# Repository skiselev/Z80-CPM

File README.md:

# Z80-CPM
RCBus Z80 CPU, 512 KiB SRAM, and 512 KiB Flash ROM module for RCBus systems designed using discrete logic

## Table of Content
* [Overview](#overview)
  * [Specifications](#specifications)
* [Assembly Instructions](#assembly-instructions)
* [Hardware Documentation](#hardware-documentation)
  * [Schematic and PCB Layout](#schematic-and-pcb-layout)
  * [Input/Output Ports](#inputoutput-ports)
  * [Connectors](#connectors)
  * [Bill of Materials](#bill-of-materials)
* [Release Notes](#release-notes)
  * [Changes](#changes)
  * [Known Issues](#known-issues)
* [Red Tape](#red-tape)
  * [Licensing](#licensing)
  * [Trademarks](#trademarks)

## Overview
Z80-CPM is an RCBus and RC2014* compatible module, designed to run [RomWBW](https://github.com/wwarthen/RomWBW) firmware including CP/M, ZSDOS, and various applications under these OSes. Z80-CPM combines functionality of the following RC2014* modules on a single module, thus saving space on the backplane:
* Z80 CPU Module
* 512k ROM 512k RAM Module - Simplified version, compatible with RomWBW firmware
* Clock and Reset Module

Minimal CP/M computer system can be built using Z80-CPM module, a backplane, and a serial port module, for example Steve Cousins' [SC716](https://smallcomputercentral.com/sc716-rcbus-z80-sio-2-serial-module/) or [SC725](https://smallcomputercentral.com/sc725-rcbus-serial-and-timer-module/) Z80 SIO modules, or MC68B50 ACIA. A Compact Flash module can be added for additional storage. For a compact system, a 3-slot [SC723](https://smallcomputercentral.com/sc723-rcbus-backplane-3/) can be used.

### Specifications
* Processor: Zilog* Z80 CPU (CMOS version - Z84C00)
* Memory: 512 KiB SRAM, 512 KiB Flash ROM, RomWBW compatible memory pager
* Bus: RCBus, RC2014* compatible
* Microprocessor Supervisor for system reset generation

## Assembly Instructions

Please refer to [Assembly Instructions](Assembly_Instructions.md) document

## Hardware Documentation

### Schematic and PCB Layout

* [Schematic - Version 1.0](KiCad/Z80-CPM-Schematic-1.0.pdf)
* [PCB Layout - Version 1.1](KiCad/Z80-CPM-Board-1.1.pdf)
* [PCB Layout - Version 1.0](KiCad/Z80-CPM-Board-1.0.pdf)

### Memory Configuration Input/Output Ports
Z80-CPM supports up to 512 KiB of RAM and up to 512 KiB of Flash ROM. It has a simple memory bank switching mechanism with two 32 KiB memory banks, inspired by Steve Cousin's [SC602](https://smallcomputercentral.com/rcbus/sc600-series/sc602-rcbus-z80-memory-module/) Memory Module. This memory bank mechanism provides minimal required functionality for the RomWBW RCZ80_std.rom image to be used without any modifications.
The upper 32 KiB bank is always mapped to the top 32 KiB of the physical RAM. The lower 32 KiB bank can be mapped to any 32 KiB size page in the physical memory. The memory page is selected by writting either 0x78 or 0x79 I/O ports, that are mapped to the same page select register.

#### 0x78 or 0x79 - Memory Page Select Register (Write-only)

Port       | Bit # | Function                               | Value
-----------|-------|----------------------------------------|-----------------------
0x78, 0x79 | 0     | Not implemented                        | Can be set to either 0 or 1
0x78, 0x79 | 5-1   | Page number for bank #0 0x0000-0xr7FFF | 0-31 - Page number
0x78, 0x79 | 7-6   | Not implemented                        | Should be set to 0

* Notes:
  * The register is reset to '0' on power-on or reset, which maps the lower 32 KiB of the Flash ROM to bank #0.
  * Bit 5 selects between the Flash ROM (bit 5 = 0) and the RAM (bit 5 = 1).

### Jumpers Settings

#### JP1 - RAM Size Configuration

Jumper Position | Description
----------------|------------
1-2             | 512 KiB SRAM
2-3             | 128 KiB SRAM

#### JP2 - Connect on-board oscillator clock to the CPU

Jumper Position | Description
----------------|------------
**Closed**      | X1 oscillator is connected to the CPU
Open            | X1 oscillator is not connected to the CPU

#### JP3 - Connect the RCBus CLK1 signal to the CPU

Jumper Position | Description
----------------|------------
**Closed**      | CLK1 signal is connected to the CPU
Open            | CLK1 signal is not connected to the CPU

#### JP2 and JP3 Configuration Notes

The module supports the following options for the CPU clock:
1. **Default**: CPU uses the clock frequency generated by the X1 oscillator, and the X1 clock frequency is output to CLK1 signal on RCBus. Install both JP2 and JP3 for this option.
2. CPU uses the clock frequency provided by another module on RCBus. Install only JP3 for this option.
3. CPU uses the clock frequency generated by the X1 oscillator, while other modules use different CLK1 signal. This might be useful, for example, when running the CPU on a frequency other than 7.3728 MHz. Install only JP2 for this option.

### Connectors

#### J1 - RC2014* Bus
Pin | Signal Name | Description                             | Pin | Signal Name | Description
--- | ----------- | --------------------------------------- | --- | ----------- | -----------
1   | A15         | Address A15; Output                    | 41  | p41         | Reserved; Not connected
2   | A14         | Address A14; Output                     | 42  | /BAI        | Bus Acknowledge In; Not connected
3   | A13         | Address A13; Output                     | 43  | /BAO        | Bus Acknowledge Out; Not connected
4   | A12         | Address A12; Output                     | 44  | p44         | Reserved; Not connected
5   | A11         | Address A11; Output                     | 45  | p45         | Reserved; Not connected
6   | A10         | Address A10; Output                     | 46  | p46         | Reserved; Not connected
7   | A9          | Address A9; Output                      | 47  | p47         | Reserved; Not connected
8   | A8          | Address A8; Output                      | 48  | p48         | Reserved; Not connected
9   | A7          | Address A7; Output                      | 49  | A23         | Address A23; Not connected
10  | A6          | Address A6; Output                      | 50  | A22         | Address A22; Not connected
11  | A5          | Address A5; Output                      | 51  | A21         | Address A21; Not connected
12  | A4          | Address A4; Output                      | 52  | A20         | Address A20; Not connected
13  | A3          | Address A3; Output                      | 53  | A19         | Address A19; Output
14  | A2          | Address A2; Output                      | 54  | A18         | Address A18; Output
15  | A1          | Address A1; Output                      | 55  | A17         | Address A17; Output
16  | A0          | Address A0; Output                      | 56  | A16         | Address A16; Output
17  | GND         | Ground                                  | 57  | GND         | Ground
18  | VCC         | Power Supply - +5V                      | 58  | VCC         | Power Supply - +5V
19  | /M1         | Machine Cycle One; Output               | 59  | /RFSH       | DRAM refresh; Output
20  | /RESET      | Reset; Output                           | 60  | PAGE         | Page ROM/RAM input; Not connected
21  | CLK1        | CPU Clock; Output                       | 61  | CLK2        | UART Clock; Not connected
22  | /INT        | Interrupt; Input                        | 62  | /BUSACK     | DMA Bus Acknowledge; Output
23  | /MREQ       | Memory Request; Output                  | 63  | /HALT       | Halt; Output
24  | /WR         | Write Request; Output                   | 64  | /BUSREQ     | DMA Bus Request; Input
25  | /RD         | Read Request; Output                    | 65  | /WAIT       | Wait; Input
26  | /IORQ       | Input/Output Request; Output            | 66  | /NMI        | Non-maskable Interrupt; Input
27  | D0          | Data D0; Input/Output                   | 67  | D8          | Data D8; Input/Output; Not connected
28  | D1          | Data D1; Input/Output                   | 68  | D9          | Data D9; Input/Output; Not connected
29  | D2          | Data D2; Input/Output                   | 69  | D10         | Data D10; Input/Output; Not connected
30  | D3          | Data D3; Input/Output                   | 70  | D11         | Data D11; Input/Output; Not connected
31  | D4          | Data D4; Input/Output                   | 71  | D12         | Data D12; Input/Output; Not connected
32  | D5          | Data D5; Input/Output                   | 72  | D13         | Data D13; Input/Output; Not connected
33  | D6          | Data D6; Input/Output                   | 73  | D14         | Data D14; Input/Output; Not connected
34  | D7          | Data D7; Input/Output                   | 74  | D15         | Data D15; Input/Output; Not connected
35  | TX          | Channel 1, Transmit Data; Not Connected | 75  | TX2         | Channel 2, Transmit Data; Not Connected
36  | RX          | Channel 1, Receive Data; Not Connected  | 76  | RX2         | Channel 2, Receive Data; Not Connected
37  | /IRQ1       | Interrupt Request 1; Not connected      | 77  | /IRQ2       | Interrupt Request 2; Not connected
38  | IEI         | Interrupt Enable In; Not connected      | 78  | p78         | Reserved; Not connected
39  | IEO         | Interrupt Enable Out; Not connected     | 79  | p79         | Reserved; Not connected
40  | USER4       | User Pin 4; Not connected               | 80  | USER8       | User Pin 8; Not connected

### Bill of Materials

#### Version 1.0

Mouser projects - All components except of the PCB and the CPU:
* [Z80-CPM project](https://www.mouser.com/Tools/Project/Share?AccessID=cf00dde769)
  * Note that optional CPU supervisor parts: U9 DS1233 CPU supervisor, C11 1 nF capacitor, and SW1 tactile switch are included in this project.

Z80-CPM project on Tindie:
* [Complete kit](https://www.tindie.com/products/weird/z80-cpm-rcbus-module-kit/).
* [Z80-CPU PCB](https://www.tindie.com/products/weird/z80-cpm-rcbus-module-pcb/).

Component type     | Reference | Description                                 | Quantity | Possible sources and notes 
------------------ | --------- | ------------------------------------------- | -------- | --------------------------
PCB                |           | Z80-CPM PCB - Version 1.0                   | 1        | Buy from my Tindie store: [Complete kit](https://www.tindie.com/products/weird/z80-cpm-rcbus-module-kit/); [Z80-CPM PCB](https://www.tindie.com/products/weird/z80-cpm-rcbus-module-pcb/), or order from a PCB manufacturer of your choice using provided Gerber or KiCad files
Integrated Circuit | U1        | Z84C00xxVEG - Z80 CPU, CMOS, 44 pin PLCC    | 1        | Mouser [692-Z84C0010VEG](https://www.mouser.com/ProductDetail/692-Z84C0010VEG)
Integrated Circuit | U2        | SST39SF040 - 512 KiB Flash ROM, 32 pin PLCC | 1        | Mouser [804-39SF0407CNHE](https://www.mouser.com/ProductDetail/804-39SF0407CNHE)
Integrated Circuit | U3        | AS6C4008 - 512 KiB SRAM, 32 pin DIP         | 1        | Mouser [913-AS6C4008-55PCN](https://www.mouser.com/ProductDetail/913-AS6C4008-55PCN)
Integrated Circuit | U4        | 74AHCT174 - Hex D-Type Flip Flop, 16 pin DIP | 1       | Mouser [595-SN74AHCT174N](https://www.mouser.com/ProductDetail/595-SN74AHCT174N)
Integrated Circuit | U5        | 74HCT138 - 3-to-8 Decoder, 16 pin DIP       | 1        | Mouser [595-CD74HCT138E](https://www.mouser.com/ProductDetail/595-CD74HCT138E)
Integrated Circuit | U6, U7    | 74AHCT32 - Quad 2-Input OR Gate, 14 pin DIP | 2        | Mouser [595-SN74AHCT32N](https://www.mouser.com/ProductDetail/595-SN74AHCT32N)
Integrated Circuit | U8        | 74AHCT00 - Quad 2-Input NAND Gate, 14 pin DIP | 1      | Mouser [595-SN74AHCT00N](https://www.mouser.com/ProductDetail/595-SN74AHCT00N)
Integrated Circuit | U9        | DS1233-5 - CPU Supervisor, 5V, TO-92-3      | 1        | Mouser [700-DS1233-5](https://www.mouser.com/ProductDetail/700-DS1233-5). Note U9 is an optional on-board CPU supervisor.
Oscillator         | X1        | 7.3728 MHz, CMOS oscillator, half can       | 1        | Mouser [774-MXO45HS-3C-7.3](https://www.mouser.com/ProductDetail/774-MXO45HS-3C-7.3) or [520-2200B-073](https://www.mouser.com/ProductDetail/520-2200B-073)
Pin Header         | J1        | 40x2 pin header, 2.54 mm pitch, right angle | 1        | Mouser [737-PH2RA-80-UA](https://www.mouser.com/ProductDetail/737-PH2RA-80-UA), [517-5121TG](https://www.mouser.com/ProductDetail/517-5121TG)
Pin Header         | JP1       | 3x1 pin header, 2.54 mm pitch, vertical     | 1        | Mouser [649-68000-203HLF](https://www.mouser.com/ProductDetail/649-68000-203HLF).
Pin Header         | JP2, JP3  | 2x2 pin header, 2.54 mm pitch, vertical     | 1        | Mouser [649-67996-104HLF](https://www.mouser.com/ProductDetail/649-67996-104HLF).
Jumper             | JP1 - JP3 | Shunt, 2 pin 2.54 mm pitch                  | 3        | Mouser [806-SX1100-B](https://www.mouser.com/ProductDetail/806-SX1100-B).
Tactile switch     | SW1       | Tactile switch, 6 mm, right angle           | 1        | Mouser [653-B3F-3152](https://www.mouser.com/ProductDetail/653-B3F-3152). SW1 is an optional reset switch.
Capacitor          | C1 - C9   | 0.1 uF, 50V, MLCC, 5 mm pitch               | 9        | Mouser [594-K104K15X7RF53H5](https://www.mouser.com/ProductDetail/594-K104K15X7RF53H5).
Capacitor          | C10        | 47 uF, 25V, electrolytic, 5 x 11 mm, 2 mm pitch | 1    | Mouser [667-EEU-FR1E470](https://www.mouser.com/ProductDetail/667-EEU-FR1E470)
Capacitor          | C11       | 1 nF, 50V, MLCC, 5 mm pitch                 | 1        | Mouser [594-K102K15X7RF5TH5](https://www.mouser.com/ProductDetail/594-K102K15X7RF5TH5). Note: C11 is optional, required if U9 installed and manual reset functionality is desired.
Resistor Array     | RN1       | 4.7 kohm, bussed, 9 pin SIP                 | 1        | Mouser [652-4609X-1LF-4.7K](https://www.mouser.com/ProductDetail/652-4609X-1LF-4.7K) or [652-4609X-AP1-472LF](https://www.mouser.com/ProductDetail/652-4609X-AP1-472LF)
Resistor Array     | RN2       | 4.7 kohm, bussed, 6 pin SIP                 | 1        | Mouser [652-4606X-1LF-4.7K](https://www.mouser.com/ProductDetail/652-4606X-1LF-4.7K) or [652-4606X-AP1-472LF](https://www.mouser.com/ProductDetail/652-4606X-AP1-472LF)
IC Socket          | U1        | 44 pin PLCC, through hole                   | 1        | Mouser [737-PLCC-44-AT](https://www.mouser.com/ProductDetail/737-PLCC-44-AT), [517-8444-11B1-RK-TP](https://www.mouser.com/ProductDetail/517-8444-11B1-RK-TP)
IC Socket          | U2        | 32 pin PLCC, through hole                   | 1        | Mouser [737-PLCC-32-AT](https://www.mouser.com/ProductDetail/737-PLCC-32-AT), [517-8432-11B1-RK-TP](https://www.mouser.com/ProductDetail/517-8432-11B1-RK-TP)
IC Socket          | U3        | 32 pin DIP                                  | 1        | Mouser [737-ICS-632-T](https://www.mouser.com/ProductDetail/737-ICS-632-T), [517-4832-6000-CP](https://www.mouser.com/ProductDetail/517-4832-6000-CP)
IC Socket          | U4, U5    | 16 pin DIP                                  | 2        | Mouser [737-ICS-316-T](https://www.mouser.com/ProductDetail/737-ICS-316-T), [517-4816-3000-CP](https://www.mouser.com/ProductDetail/517-4816-3000-CP).
IC Socket          | U6 - U8   | 14 pin DIP                                  | 3        | Mouser [737-ICS-314-T](https://www.mouser.com/ProductDetail/737-ICS-314-T), [517-4816-3000-CP](https://www.mouser.com/ProductDetail/517-4816-3000-CP).
Oscillator Socket  | X1        | 4 pin DIP, Half Can                         | 1        | Mouser [535-1108800](https://www.mouser.com/ProductDetail/535-1108800)

## Release Notes

### Changes

* Version 1.1
  * Fix cosmetic issues:
    * Swap C5 with C8 and C4 with C6.
    * Modify C10 footpring to clearly show negative terminal.

* Version 1.0
  * Initial version.

### Known Issues

* Version 1.0
  * Cosmetic issues:
    * C5 and C8, and C6 and C4 should be swapped.
    * C10 should have more clear marking for the negative terminal.

## Red Tape

### Licensing

Z80-CPM is an open source hardware project. The hardware design itself, including schematic and PCB layout design files are licensed under the strongly-reciprocal variant of [CERN Open Hardware Licence version 2](license-cern_ohl_s_v2.txt). Documentation, including this file, is licensed under the [Creative Commons Attribution-ShareAlike 4.0 International License](license-cc-by-sa-4.0.txt).

### Trademarks

* "RC2014" is a registered trademark of RFC2795 Ltd.
* Other names and brands may be claimed as the property of others.

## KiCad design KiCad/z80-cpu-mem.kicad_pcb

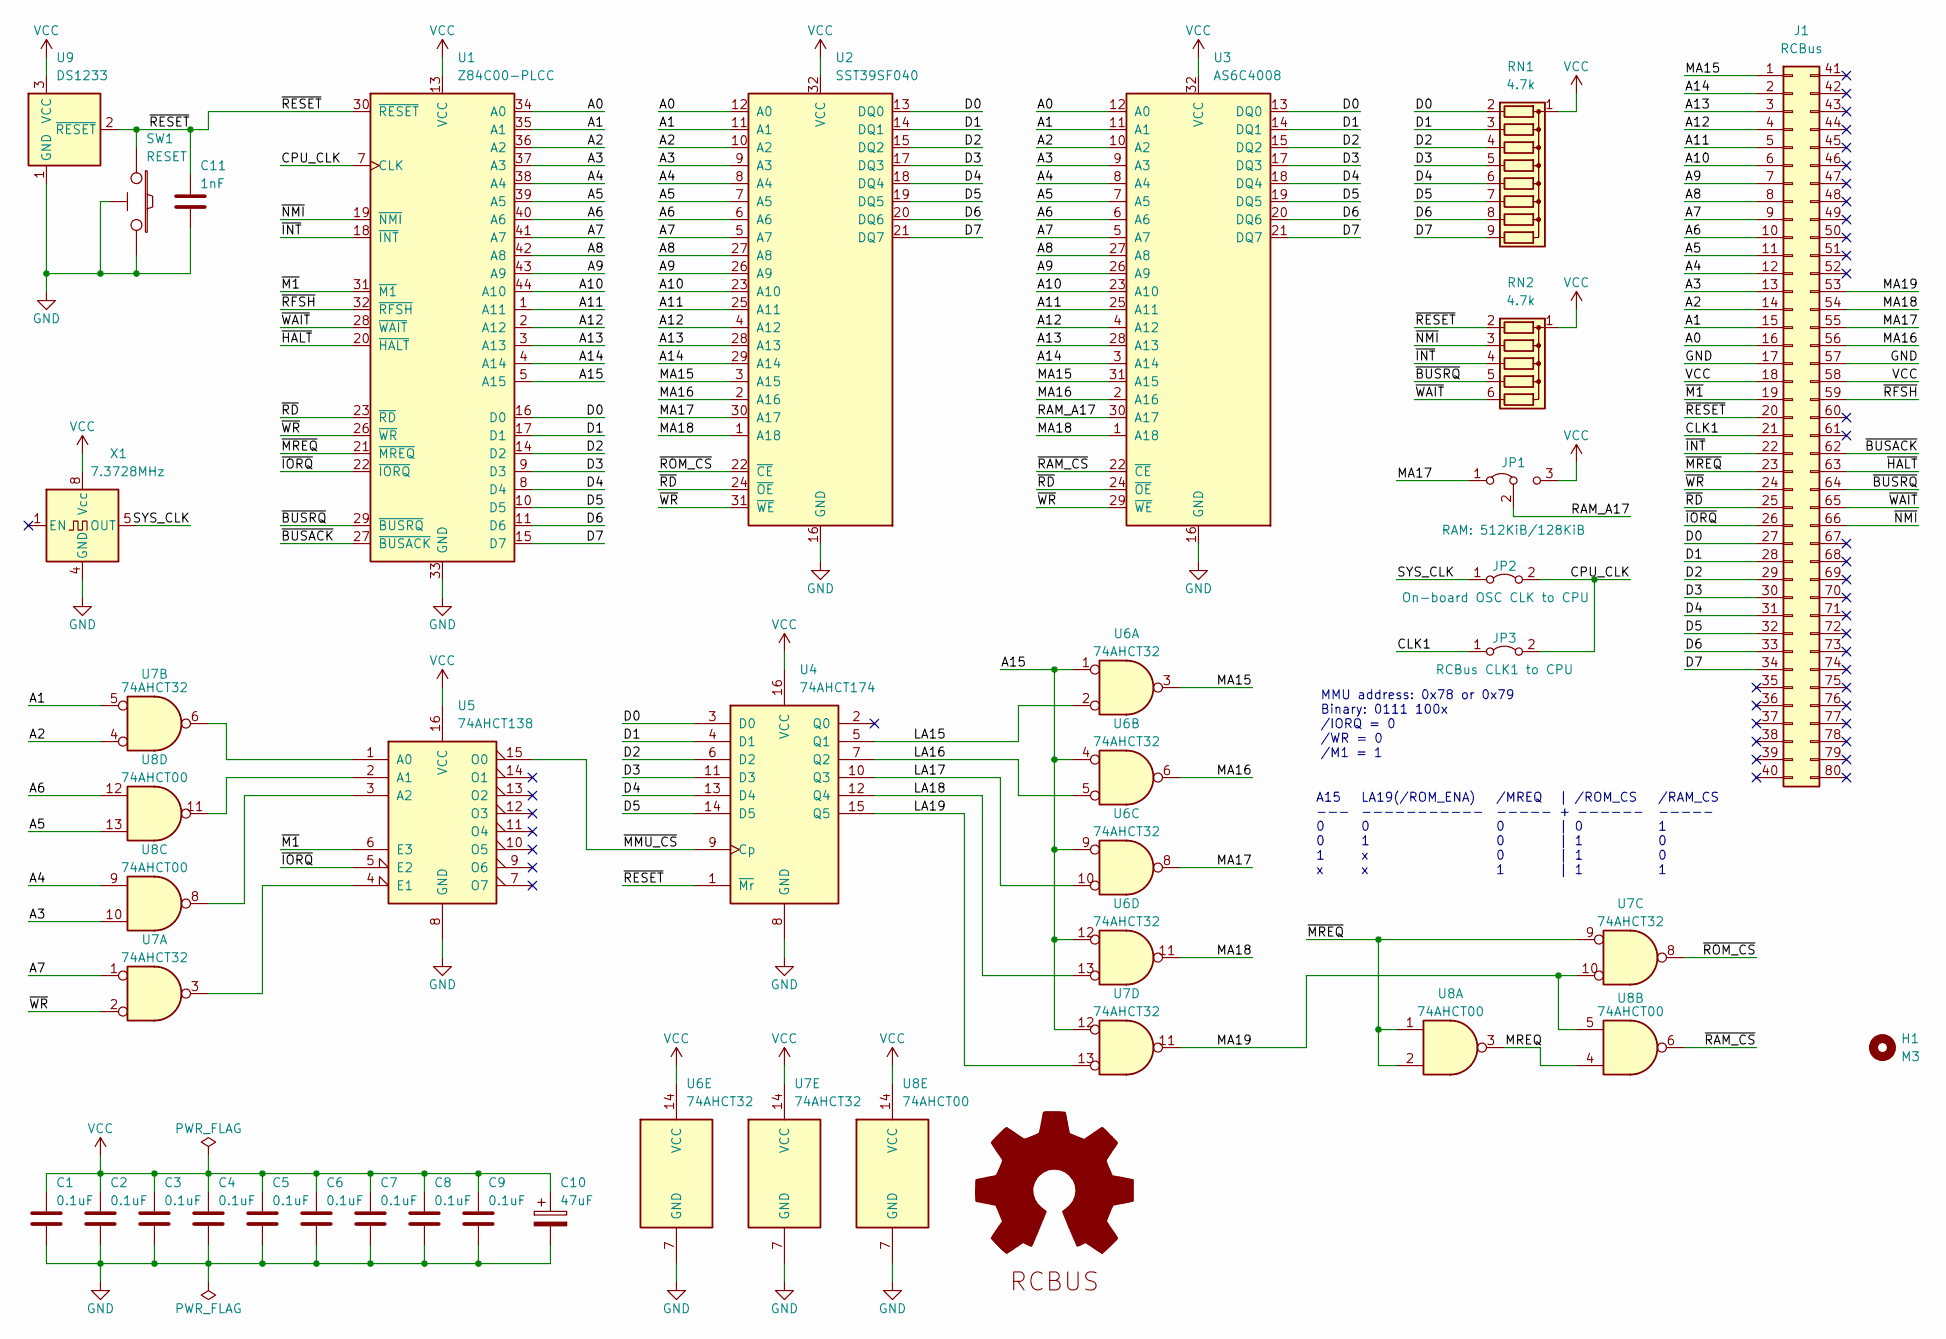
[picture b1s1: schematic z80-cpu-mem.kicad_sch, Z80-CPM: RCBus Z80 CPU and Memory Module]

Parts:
C1, C2, C3, C4, C5, C6, C7, C8, C9: 0.1uF; Cap_Cer_508
C10: 47uF; Cap_Elec_Radial_5mm
C11: 1nF; Cap_Cer_508
H1: M3; MountingHole_3.2mm_M3_DIN965
J1: RCBus; Conn_Pin_Header_40x2_2.54mm_Right_Angle_RCBus80
JP1: RAM: 512KiB/128KiB; Conn_Pin_Header_3x1_2.54mm
JP2: On-board OSC CLK to CPU; Conn_Pin_Header_2x1_2.54mm
JP3: RCBus CLK1 to CPU; Conn_Pin_Header_2x1_2.54mm
LOGO1: Logo_Open_Hardware_Large; OSHW-Logo2_7.3x6mm_SilkScreen
LOGO2: RCBUS_Logo
RN1: 4.7k; Conn_SIL9
RN2: 4.7k; Conn_SIL6
SW1: RESET; Switch_Tactile_6mm_Right
U1: Z84C00-PLCC; IC_PLCC44_TH
U2: SST39SF040; IC_PLCC32_TH
U3: AS6C4008; IC_DIP32_600
U4: 74AHCT174; IC_DIP16_300
U5: 74AHCT138; IC_DIP16_300
U6, U7: 74AHCT32; IC_DIP14_300
U8: 74AHCT00; IC_DIP14_300
U9: DS1233; Transistor_TO92_EBC_254
X1: 7.3728MHz; OSC_Half_Can_DIP8

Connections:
/A0: J1.16, U1.34 (A0), U2.12 (A0), U3.12 (A0)
/A1: J1.15, U1.35 (A1), U2.11 (A1), U3.11 (A1), U7.5
/A2: J1.14, U1.36 (A2), U2.10 (A2), U3.10 (A2), U7.4
/A3: J1.13, U1.37 (A3), U2.9 (A3), U3.9 (A3), U8.10
/A4: J1.12, U1.38 (A4), U2.8 (A4), U3.8 (A4), U8.9
/A5: J1.11, U1.39 (A5), U2.7 (A5), U3.7 (A5), U8.13
/A6: J1.10, U1.40 (A6), U2.6 (A6), U3.6 (A6), U8.12
/A7: J1.9, U1.41 (A7), U2.5 (A7), U3.5 (A7), U7.1
/A8: J1.8, U1.42 (A8), U2.27 (A8), U3.27 (A8)
/A9: J1.7, U1.43 (A9), U2.26 (A9), U3.26 (A9)
/A10: J1.6, U1.44 (A10), U2.23 (A10), U3.23 (A10)
/A11: J1.5, U1.1 (A11), U2.25 (A11), U3.25 (A11)
/A12: J1.4, U1.2 (A12), U2.4 (A12), U3.4 (A12)
/A13: J1.3, U1.3 (A13), U2.28 (A13), U3.28 (A13)
/A14: J1.2, U1.4 (A14), U2.29 (A14), U3.3 (A14)
/A15: U1.5 (A15), U6.1, U6.4, U6.9, U6.12, U7.12
/CLK1: J1.21, JP3.1 (A)
/CPU_CLK: JP2.2 (B), JP3.2 (B), U1.7 (CLK)
/D0: J1.27, RN1.2 (R1), U1.16 (D0), U2.13 (DQ0), U3.13 (DQ0), U4.3 (D0)
/D1: J1.28, RN1.3 (R2), U1.17 (D1), U2.14 (DQ1), U3.14 (DQ1), U4.4 (D1)
/D2: J1.29, RN1.4 (R3), U1.14 (D2), U2.15 (DQ2), U3.15 (DQ2), U4.6 (D2)
/D3: J1.30, RN1.5 (R4), U1.9 (D3), U2.17 (DQ3), U3.17 (DQ3), U4.11 (D3)
/D4: J1.31, RN1.6 (R5), U1.8 (D4), U2.18 (DQ4), U3.18 (DQ4), U4.13 (D4)
/D5: J1.32, RN1.7 (R6), U1.10 (D5), U2.19 (DQ5), U3.19 (DQ5), U4.14 (D5)
/D6: J1.33, RN1.8 (R7), U1.11 (D6), U2.20 (DQ6), U3.20 (DQ6)
/D7: J1.34, RN1.9 (R8), U1.15 (D7), U2.21 (DQ7), U3.21 (DQ7)
/LA15: U4.5 (Q1), U6.2
/LA16: U4.7 (Q2), U6.5
/LA17: U4.10 (Q3), U6.10
/LA18: U4.12 (Q4), U6.13
/LA19: U4.15 (Q5), U7.13
/MA15: J1.1, U2.3 (A15), U3.31 (A15), U6.3
/MA16: J1.56, U2.2 (A16), U3.2 (A16), U6.6
/MA17: J1.55, JP1.1 (A), U2.30 (A17), U6.8
/MA18: J1.54, U2.1 (A18), U3.1 (A18), U6.11
/MA19: J1.53, U7.10, U7.11, U8.5
/MREQ: U8.3, U8.4
/RAM_A17: JP1.2 (C), U3.30 (A17)
/SYS_CLK: JP2.1 (A), X1.5 (OUT)
/~BUSACK: J1.62, U1.27 (~BUSACK)
/~BUSRQ: J1.64, RN2.5 (R4), U1.29 (~BUSRQ)
/~HALT: J1.63, U1.20 (~HALT)
/~INT: J1.22, RN2.4 (R3), U1.18 (~INT)
/~IORQ: J1.26, U1.22 (~IORQ), U5.5 (E2)
/~M1: J1.19, U1.31 (~M1), U5.6 (E3)
/~MMU_CS: U4.9 (Cp), U5.15 (O0)
/~MREQ: J1.23, U1.21 (~MREQ), U7.9, U8.1, U8.2
/~NMI: J1.66, RN2.3 (R2), U1.19 (~NMI)
/~RAM_CS: U3.22 (~CE), U8.6
/~RD: J1.25, U1.23 (~RD), U2.24 (~OE), U3.24 (~OE)
/~RESET: C11.1, J1.20, RN2.2 (R1), SW1.1, U1.30 (~RESET), U4.1 (~Mr), U9.2 (~RESET)
/~RFSH: J1.59, U1.32 (~RFSH)
/~ROM_CS: U2.22 (~CE), U7.8
/~WAIT: J1.65, RN2.6 (R5), U1.28 (~WAIT)
/~WR: J1.24, U1.26 (~WR), U2.31 (~WE), U3.29 (~WE), U7.2
GND: C1.2, C2.2, C3.2, C4.2, C5.2, C6.2, C7.2, C8.2, C9.2, C10.2, C11.2, J1.17, J1.57, SW1.2, SW1.GND, U1.33 (GND), U2.16 (GND), U3.16 (GND), U4.8 (GND), U5.8 (GND), U6.7 (GND), U7.7 (GND), U8.7 (GND), U9.1 (GND), X1.4 (GND)
unnamed: U5.1 (A0), U7.6
unnamed: U5.2 (A1), U8.11
unnamed: U5.3 (A2), U8.8
unnamed: U5.4 (E1), U7.3
VCC: C1.1, C2.1, C3.1, C4.1, C5.1, C6.1, C7.1, C8.1, C9.1, C10.1, J1.18, J1.58, JP1.3 (B), RN1.1 (common), RN2.1 (common), U1.13 (VCC), U2.32 (VCC), U3.32 (VCC), U4.16 (VCC), U5.16 (VCC), U6.14 (VCC), U7.14 (VCC), U8.14 (VCC), U9.3 (VCC), X1.8 (Vcc)

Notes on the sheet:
/RAM_CS ----- 1 0 0 1
LA19(/ROM_ENA) ----------- 0 1 x x
MMU address: 0x78 or 0x79 Binary: 0111 100x /IORQ = 0 /WR = 0 /M1 = 1
/MREQ ----- 0 0 0 1
A15 --- 0 0 1 x
| /ROM_CS + ------ | 0 | 1 | 1 | 1

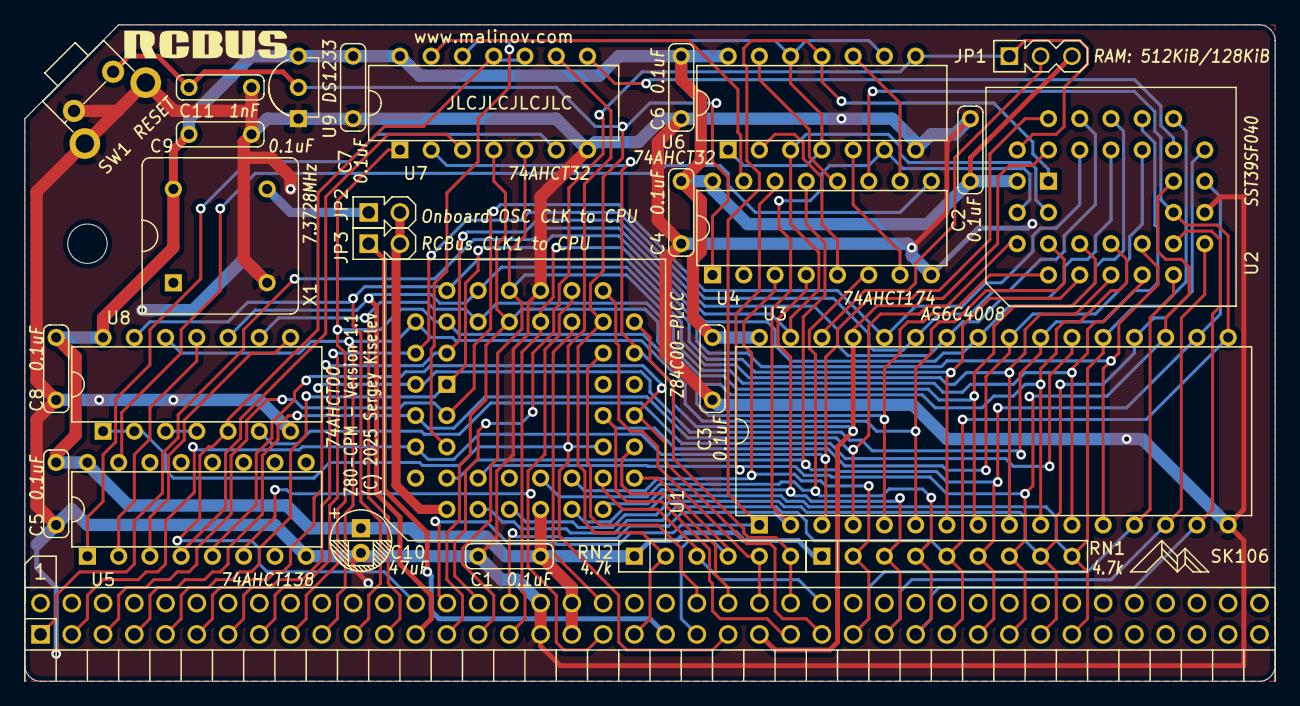
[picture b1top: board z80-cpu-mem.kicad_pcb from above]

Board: 2 copper layers, 101.6 x 53.3 mm, 31 parts (1 on the bottom side), 61 nets.

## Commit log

2025-06-30 Add v1.0 files
2025-06-30 Minor updates to README
2025-06-30 Add files for v1.1
2025-06-30 Minor README updates
2025-11-29 README: Update kit description
2025-11-29 README: Update comments in BoM

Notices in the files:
README.md:
Licensing:
Z80-CPM is an open source hardware project. The hardware design itself, including schematic and PCB layout design files are licensed under the strongly-reciprocal variant of [CERN Open Hardware Licence version 2](license-cern_ohl_s_v2.txt). Documentation, including this file, is licensed under the [Creative Commons Attribution-ShareAlike 4.0 International License](license-cc-by-sa-4.0.txt).
KiCad/z80-cpu-mem.kicad_pcb:
Licensed under CERN-OHL-S: https://cern-ohl.web.cern.ch
(C) 2025 Sergey Kiselev
